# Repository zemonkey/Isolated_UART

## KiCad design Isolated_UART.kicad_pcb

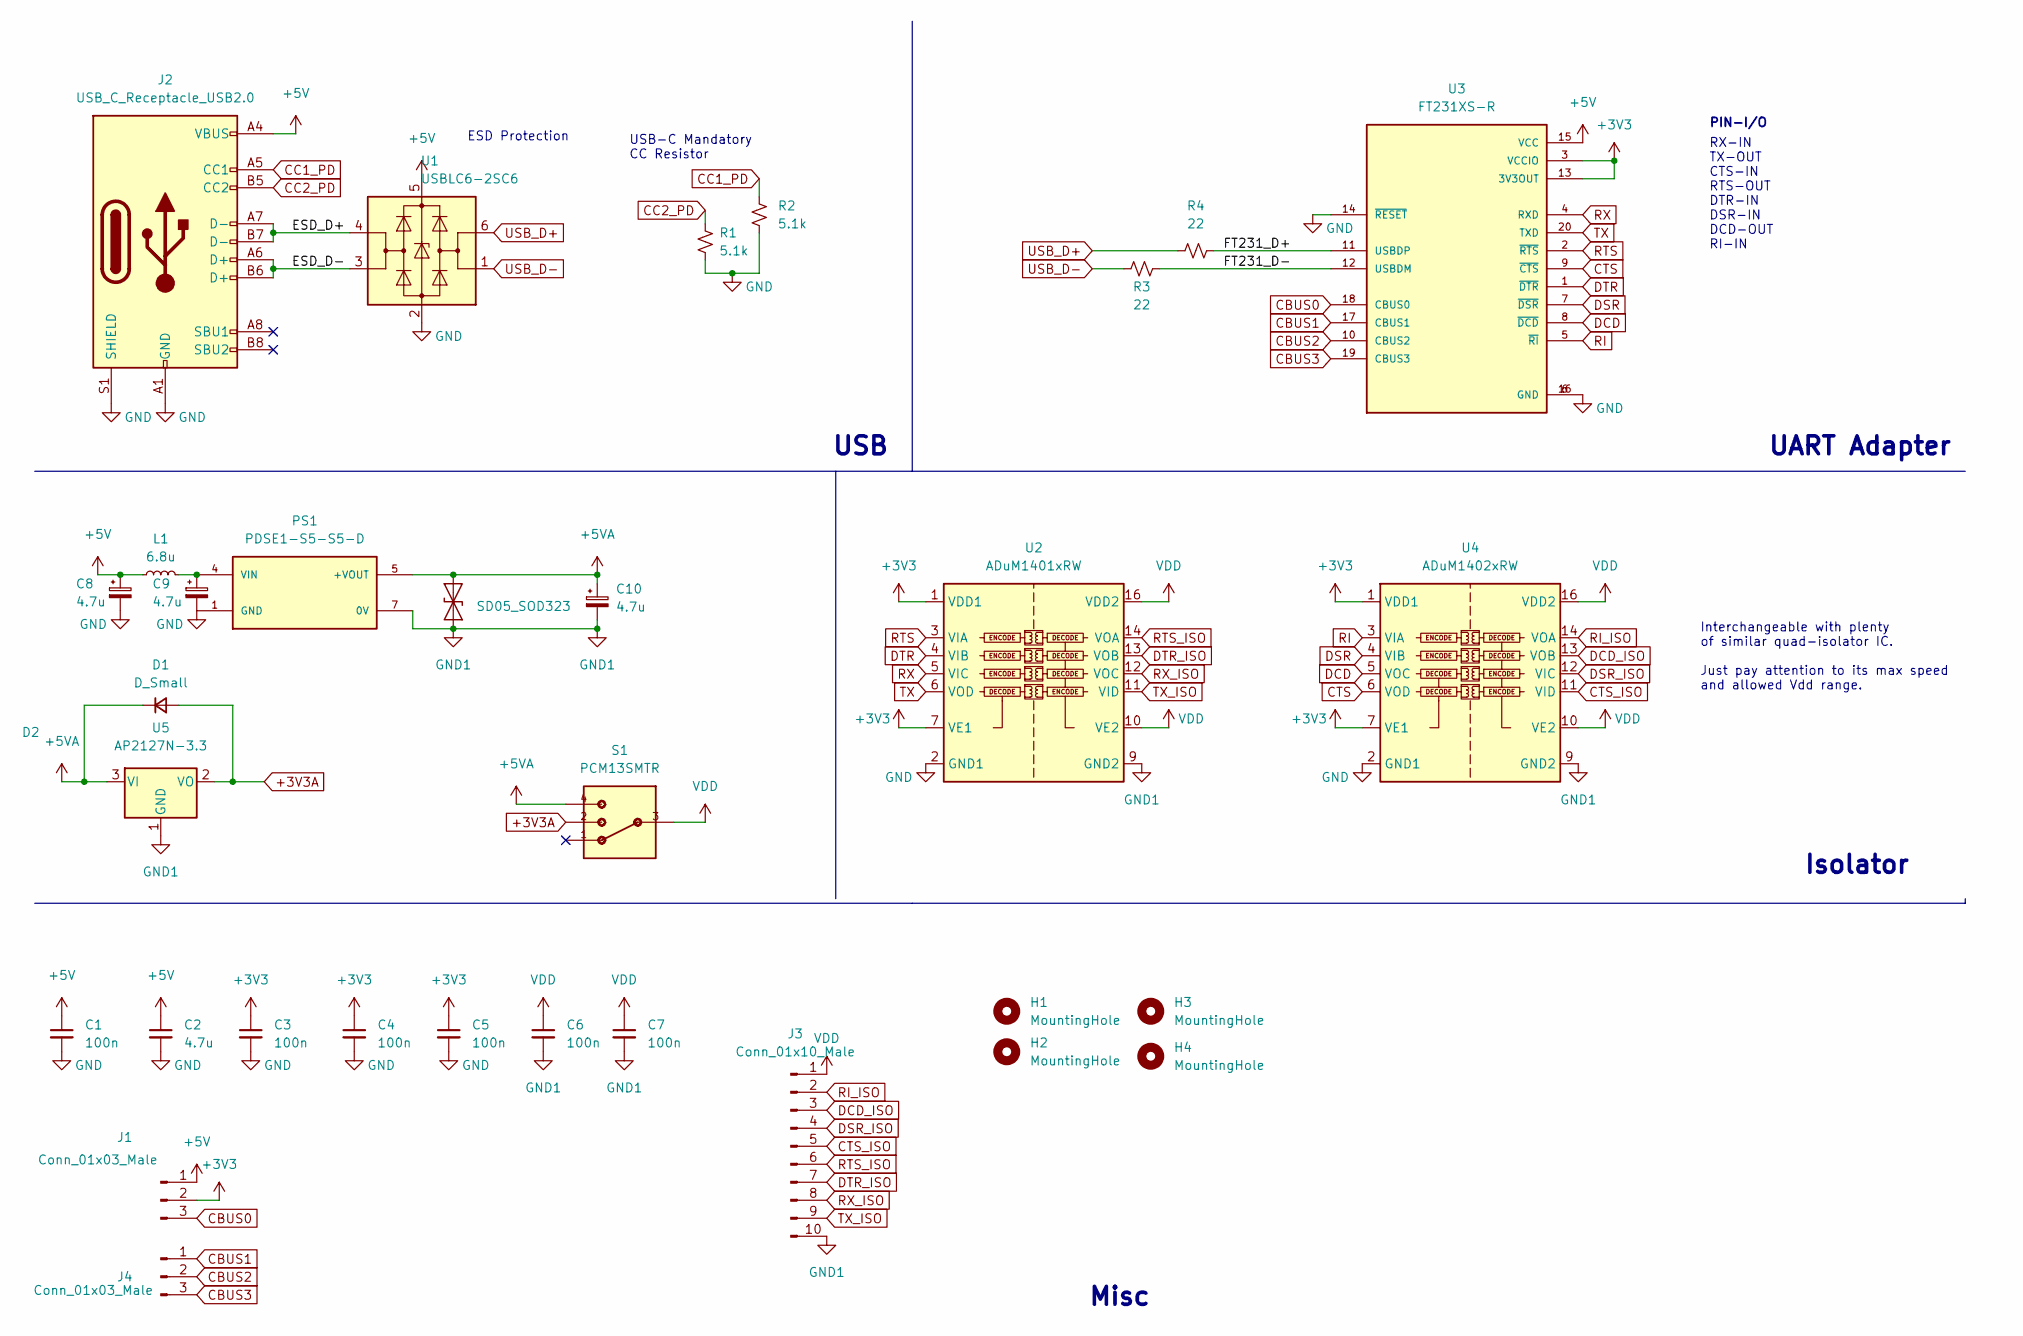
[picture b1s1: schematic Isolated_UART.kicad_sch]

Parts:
C1, C3, C4, C5, C6, C7: 100n; C_0603_1608Metric_Pad1.08x0.95mm_HandSolder
C2: 4.7u; C_0603_1608Metric_Pad1.08x0.95mm_HandSolder
C8, C9, C10: 4.7u; CP_Radial_D5.0mm_P2.00mm
D1: D_Small; D_SOD-323_HandSoldering
D2: SD05_SOD323; D_SOD-323
H1, H2, H3, H4: MountingHole; MountingHole_3.2mm_M3_DIN965
J1, J4: Conn_01x03_Male; PinHeader_1x03_P2.54mm_Vertical
J2: USB_C_Receptacle_USB2.0; USB_C_Receptacle_XKB_U262-16XN-4BVC11
J3: Conn_01x10_Male; PinHeader_1x10_P2.54mm_Vertical
L1: 6.8u; L_Wuerth_HCI-5040
PS1: PDSE1-S5-S5-D; CONV_PDSE1-S5-S5-D; PARTREV 1.03
R1, R2: 5.1k; R_0805_2012Metric_Pad1.20x1.40mm_HandSolder
R3, R4: 22; R_0805_2012Metric_Pad1.20x1.40mm_HandSolder
S1: PCM13SMTR; SW_PCM13SMTR
U1: USBLC6-2SC6; SOT-23-6
U2: ADuM1401xRW; SOIC-16W_7.5x10.3mm_P1.27mm
U3: FT231XS-R; SOP63P599X175-20N; PARTREV 1.2
U4: ADuM1402xRW; SOIC-16W_7.5x10.3mm_P1.27mm
U5: AP2127N-3.3; SOT-23

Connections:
+3V3: C3.1, C4.1, C5.1, J1.2, U2.1 (VDD1), U2.7 (VE1), U3.3 (VCCIO), U3.13 (3V3OUT), U4.1 (VDD1), U4.7 (VE1)
+3V3A: D1.2 (A), S1.2, U5.2 (VO)
+5V: C1.1, C2.1, C8.1, J1.1, J2.A4 (VBUS), J2.A9 (VBUS), J2.B4 (VBUS), J2.B9 (VBUS), L1.1, U1.5 (VBUS), U3.15 (VCC)
+5VA: C10.1, D1.1 (K), D2.2 (A2), PS1.5 (+VOUT), S1.4, U5.3 (VI)
/ESD_D+: J2.A7 (D-), J2.B7 (D-), U1.4 (I/O2)
/ESD_D-: J2.A6 (D+), J2.B6 (D+), U1.3 (I/O2)
/FT231_D+: R4.2, U3.11 (USBDP)
/FT231_D-: R3.2, U3.12 (USBDM)
CBUS0: J1.3, U3.18 (CBUS0)
CBUS1: J4.1, U3.17 (CBUS1)
CBUS2: J4.2, U3.10 (CBUS2)
CBUS3: J4.3, U3.19 (CBUS3)
CC1_PD: J2.A5 (CC1), R2.1
CC2_PD: J2.B5 (CC2), R1.2
CTS: U3.9 (~CTS), U4.6 (VOD)
CTS_ISO: J3.5, U4.11 (VID)
DCD: U3.8 (~DCD), U4.5 (VOC)
DCD_ISO: J3.3, U4.13 (VOB)
DSR: U3.7 (~DSR), U4.4 (VIB)
DSR_ISO: J3.4, U4.12 (VIC)
DTR: U2.4 (VIB), U3.1 (~DTR)
DTR_ISO: J3.7, U2.13 (VOB)
GND: C1.2, C2.2, C3.2, C4.2, C5.2, C8.2, C9.2, J2.A1 (GND), J2.A12 (GND), J2.B1 (GND), J2.B12 (GND), J2.S1 (SHIELD), PS1.1 (GND), R1.1, R2.2, U1.2 (GND), U2.2 (GND1), U2.8 (GND1), U3.6 (GND), U3.14 (~RESET), U3.16 (GND), U4.2 (GND1), U4.8 (GND1)
GND1: C6.2, C7.2, C10.2, D2.1 (A1), J3.10, PS1.7 (0V), U2.9 (GND2), U2.15 (GND2), U4.9 (GND2), U4.15 (GND2), U5.1 (GND)
unnamed: C9.1, L1.2, PS1.4 (VIN)
RI: U3.5 (~RI), U4.3 (VIA)
RI_ISO: J3.2, U4.14 (VOA)
RTS: U2.3 (VIA), U3.2 (~RTS)
RTS_ISO: J3.6, U2.14 (VOA)
RX: U2.5 (VIC), U3.4 (RXD)
RX_ISO: J3.8, U2.12 (VOC)
TX: U2.6 (VOD), U3.20 (TXD)
TX_ISO: J3.9, U2.11 (VID)
USB_D+: R4.1, U1.6 (I/O1)
USB_D-: R3.1, U1.1 (I/O1)
VDD: C6.1, C7.1, J3.1, S1.3, U2.10 (VE2), U2.16 (VDD2), U4.10 (VE2), U4.16 (VDD2)

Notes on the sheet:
USB-C Mandatory CC Resistor
Interchangeable with plenty of similar quad-isolator IC. Just pay attention to its max speed and allowed Vdd range.
ESD Protection
USB
Misc
UART Adapter
Isolator
RX-IN TX-OUT CTS-IN RTS-OUT DTR-IN DSR-IN DCD-OUT RI-IN
PIN-I/O

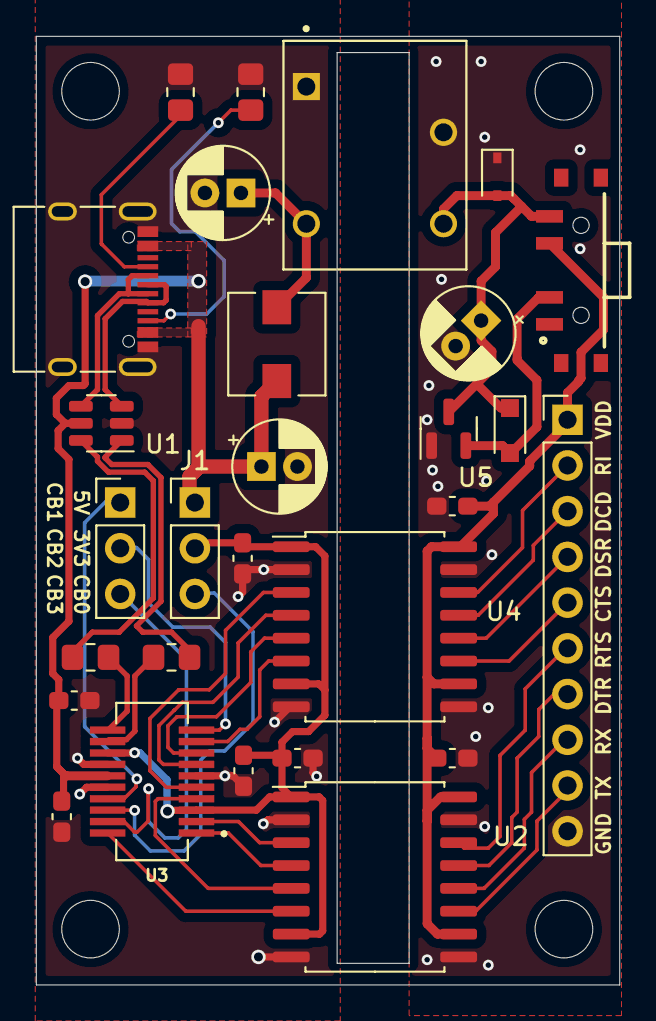
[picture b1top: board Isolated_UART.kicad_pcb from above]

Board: 2 copper layers, 32.4 x 52.7 mm, 32 parts (0 on the bottom side), 36 nets.

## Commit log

2022-06-12 Revised the schematic for clarity
